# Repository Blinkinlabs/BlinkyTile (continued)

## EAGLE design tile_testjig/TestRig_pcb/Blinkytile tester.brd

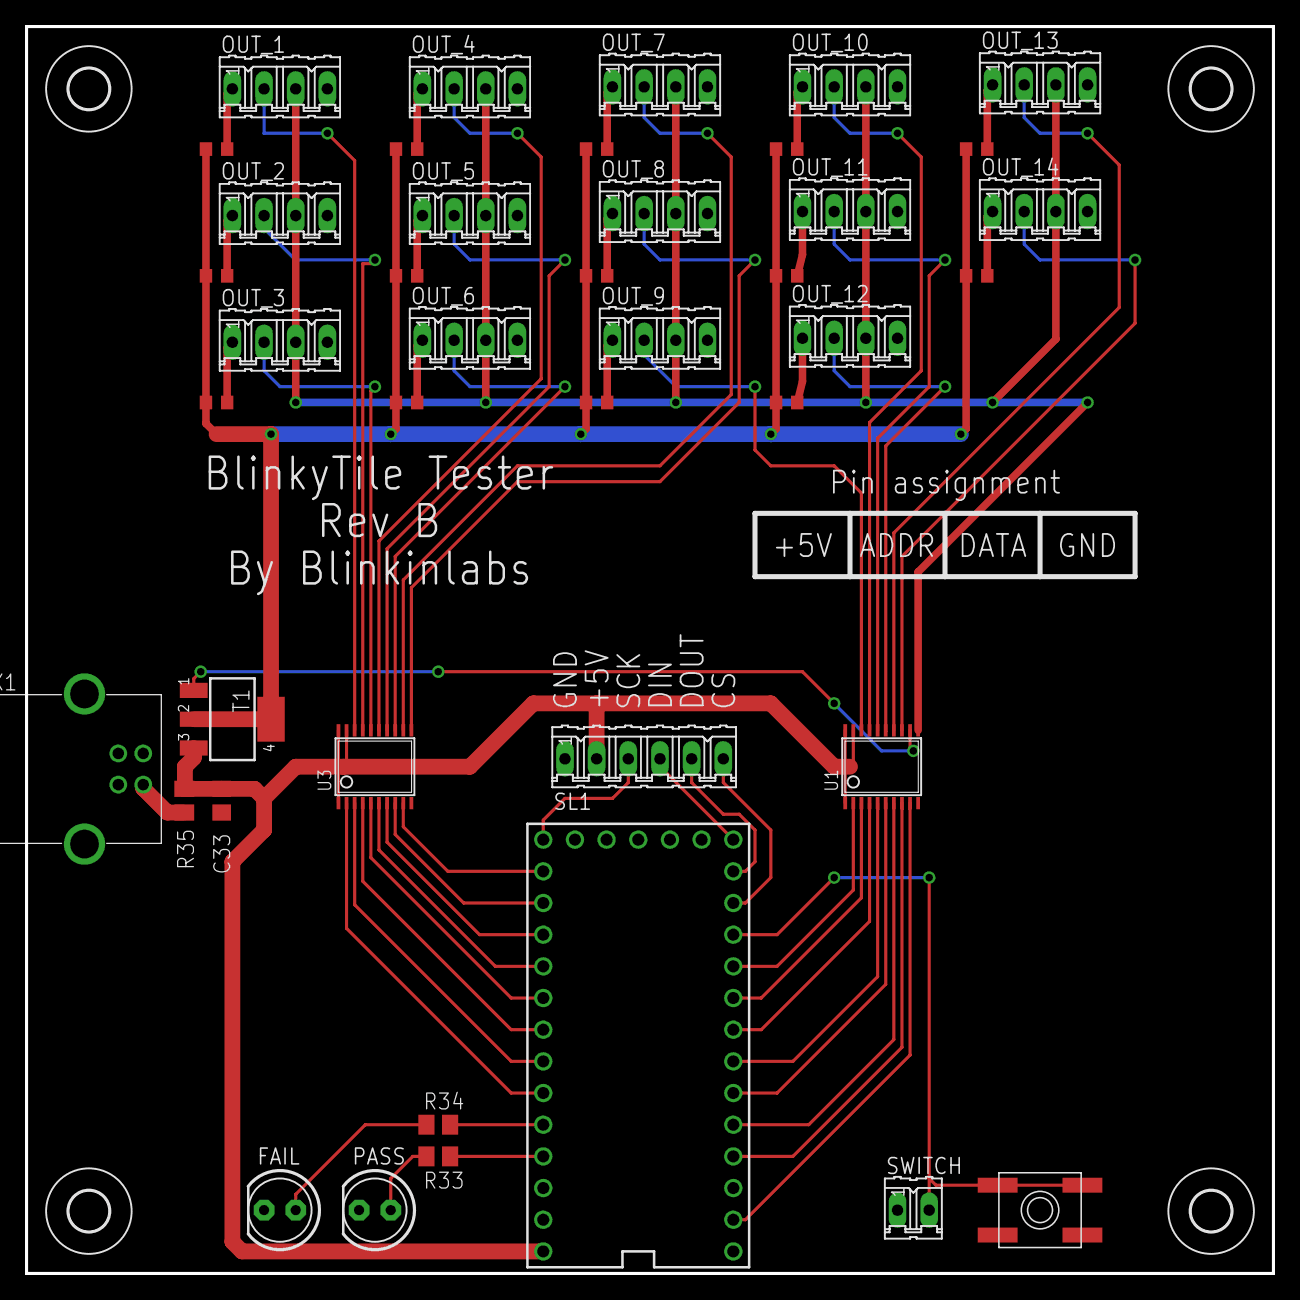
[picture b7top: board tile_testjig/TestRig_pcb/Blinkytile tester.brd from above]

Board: 2 copper layers, 100.0 x 100.0 mm, 46 parts (0 on the bottom side), 60 nets.

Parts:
C33: 0.1uF; C0805
FAIL: LED5MM
H1, H2, H3, H4: MOUNT-HOLE3.2; 3,2
OUT_1, OUT_2, OUT_3, OUT_4, OUT_5, OUT_6, OUT_7, OUT_8, OUT_9, OUT_10, OUT_11, OUT_12, OUT_13, OUT_14: 04P
PASS: LED5MM
R1, R2, R3, R4, R5, R6, R7, R8, R9, R10, R11, R12, R13, R14: 50; R0603
R33, R34, R35: M0805
SL1: 06P
SW1: SPST_TACT-EVQQ2; EVQ-Q2
SWITCH: 02P
T1: SOT223
U1, U3: SN74HCT245PWR; TSSOP20
U$1: TEENSY_3.0_BASIC
X1: MINI-USB_4P-85-32004-10X; 85-32004-10X

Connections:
3.3V: U$1.3.3V, U$1.3.3V1
5V_B: R1.1, R2.1, R3.1, R4.1, R5.1, R6.1, R7.1, R8.1, R9.1, R10.1, R11.1, R12.1, R13.1, R14.1, T1.2, T1.4
+5V: C33.1, R35.2, SL1.2, T1.3, U1.1, U1.19, U1.20, U3.1, U3.19, U3.20, U$1.VIN
ADDR1: U3.2, U$1.21/A7
ADDR1_B: OUT_1.2, U3.18
ADDR2: U3.3, U$1.20/A6
ADDR2_B: OUT_2.2, U3.17
ADDR3: U3.4, U$1.19/A5
ADDR3_B: OUT_3.2, U3.16
ADDR4: U3.5, U$1.18/A4
ADDR4_B: OUT_4.2, U3.15
ADDR5: U3.6, U$1.17/A3
ADDR5_B: OUT_5.2, U3.14
ADDR6: U3.7, U$1.16/A2
ADDR6_B: OUT_6.2, U3.13
ADDR7: U3.8, U$1.15/A1
ADDR7_B: OUT_7.2, U3.12
ADDR8: U3.9, U$1.14/A0
ADDR8_B: OUT_8.2, U3.11
ADDR9: U1.2, U$1.8
ADDR9_B: OUT_9.2, U1.18
ADDR10: U1.3, U$1.7
ADDR10_B: OUT_10.2, U1.17
ADDR11: U1.4, U$1.6
ADDR11_B: OUT_11.2, U1.16
ADDR12: U1.5, U$1.5
ADDR12_B: OUT_12.2, U1.15
ADDR13: U1.6, U$1.4
ADDR13_B: OUT_13.2, U1.14
ADDR14: U1.7, U$1.3
ADDR14_B: OUT_14.2, U1.13
CS: SL1.6, U$1.10
DATA: U1.9, U$1.0
DATA_B: OUT_1.3, OUT_2.3, OUT_3.3, OUT_4.3, OUT_5.3, OUT_6.3, OUT_7.3, OUT_8.3, OUT_9.3, OUT_10.3, OUT_11.3, OUT_12.3, OUT_13.3, OUT_14.3, U1.11
DIN: SL1.4, U$1.12
DOUT: SL1.5, U$1.11
GND: C33.2, FAIL.K, OUT_1.4, OUT_2.4, OUT_3.4, OUT_4.4, OUT_5.4, OUT_6.4, OUT_7.4, OUT_8.4, OUT_9.4, OUT_10.4, OUT_11.4, OUT_12.4, OUT_13.4, OUT_14.4, PASS.K, SL1.1, SW1.A, SW1.A', SWITCH.1, U1.10, U3.10, U$1.AGND, U$1.GND, U$1.GND1, X1.4
GOOD: PASS.A, R33.1
unnamed: OUT_5.1, R5.2
unnamed: OUT_1.1, R1.2
unnamed: SW1.B, SW1.B', SWITCH.2, U$1.9
unnamed: OUT_2.1, R2.2
unnamed: OUT_3.1, R3.2
unnamed: OUT_4.1, R4.2
unnamed: OUT_6.1, R6.2
unnamed: OUT_7.1, R7.2
unnamed: OUT_8.1, R8.2
unnamed: OUT_9.1, R9.2
unnamed: OUT_10.1, R10.2
unnamed: OUT_11.1, R11.2
unnamed: OUT_13.1, R13.2
unnamed: OUT_14.1, R14.2
unnamed: OUT_12.1, R12.2
unnamed: R33.2, U$1.23/A9
unnamed: R34.2, U$1.22/A8
unnamed: FAIL.A, R34.1
unnamed: R35.1, X1.1
PWR_EN: U1.8, U$1.2
PWR_EN_B: T1.1, U1.12
SCK: SL1.3, U$1.13

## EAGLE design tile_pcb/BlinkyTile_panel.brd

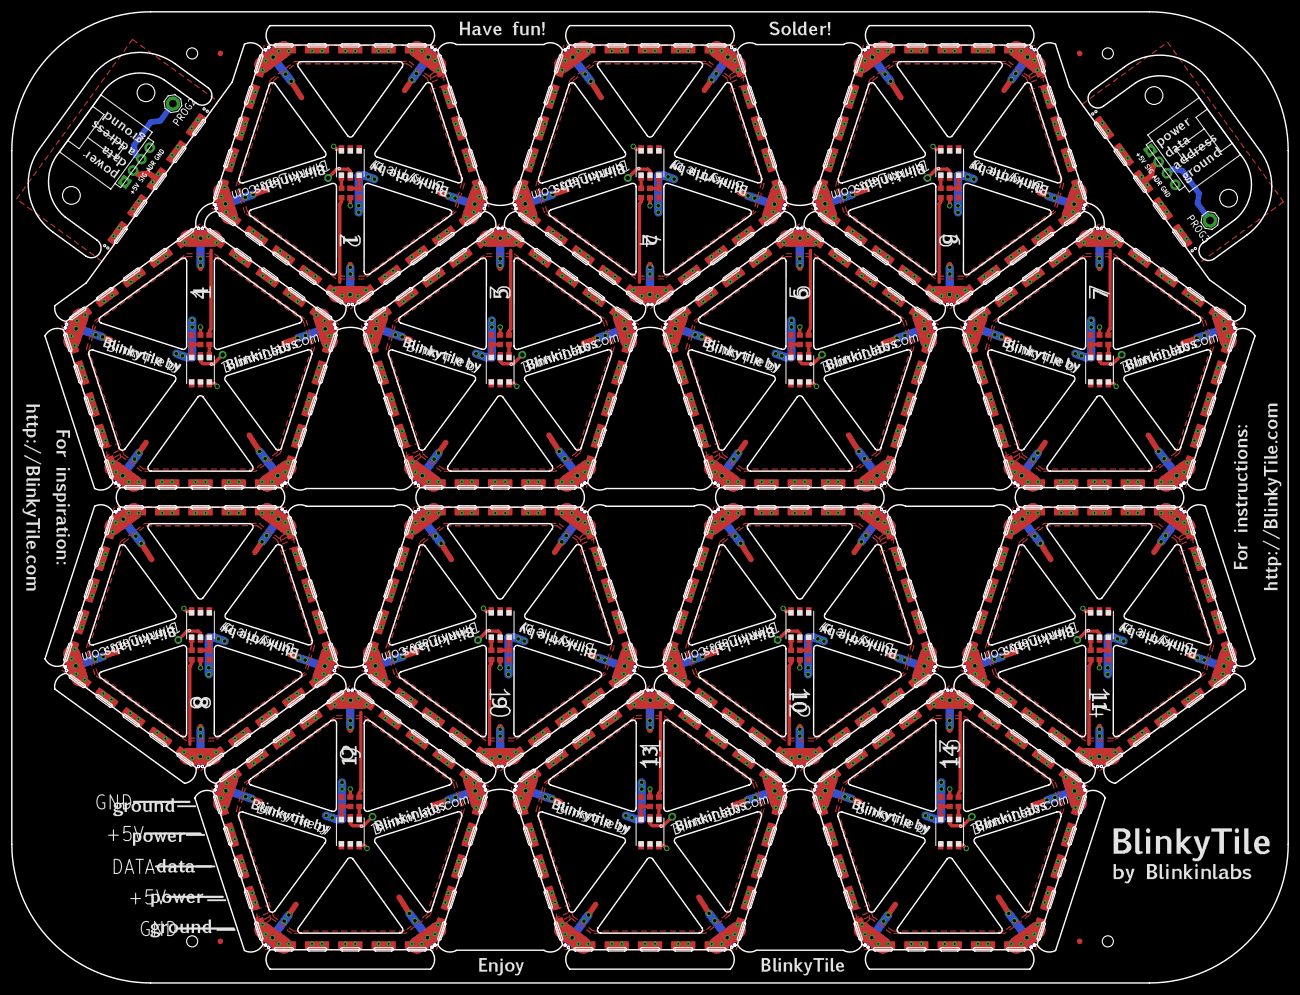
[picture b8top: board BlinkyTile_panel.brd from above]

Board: 2 copper layers, 230.0 x 175.0 mm, 322 parts (0 on the bottom side), 78 nets.

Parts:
C2, C3, C4, C5, C6, C7, C8, C9, C10, C11, C12, C13, C14, C15: .1uF; C0603
E$1, E$2, E$221, E$224: FIDUCIAL-1X2
E$23, E$24, E$25, E$26, E$27, E$28, E$29, E$30, E$31, E$32, E$33, E$34, E$35, E$36, E$37, E$38, E$39, E$40, E$41, E$42, E$43, E$44, E$45, E$46, E$49, E$50, E$51, E$52, E$53, E$54, E$56, E$57, E$58, E$59, E$60, E$61, E$62, E$63, E$64, E$65, E$66, E$67, E$68, E$69, E$70, E$71, E$72, E$73, E$74, E$75, E$76, E$77, E$78, E$79, E$80, E$81, E$82, E$83, E$84, E$85, E$86, E$87, E$88, E$89, E$90, E$91, E$92, E$93, E$94, E$95, E$96, E$97, E$98, E$99, E$100, E$101, E$102, E$103, E$104, E$105, E$106, E$107, E$108, E$109, E$110, E$111, E$112, E$113, E$114, E$115, E$116, E$117, E$118, E$119, E$120, E$121, E$122, E$123, E$124, E$125, E$126, E$127, E$128, E$129, E$130, E$131, E$132, E$133, E$134, E$135, E$136, E$137, E$138, E$139, E$140, E$141, E$142, E$143, E$144, E$145, E$146, E$147, E$148, E$149, E$150, E$151, E$152, E$153, E$154, E$155, E$156, E$157, E$158, E$159, E$160, E$161, E$162, E$163, E$164, E$165, E$166, E$167, E$168, E$169, E$170, E$171, E$172, E$173, E$174, E$175, E$176, E$177, E$178, E$179, E$180, E$181, E$182, E$183, E$184, E$185, E$186, E$187, E$188, E$189, E$190, E$191, E$192, E$193, E$199, E$200, E$202, E$203: MOUSE_BITE_1
E$201, E$204: 4-PIN_DUPONT
E$205, E$206, E$207, E$208, E$209, E$210, E$211, E$212, E$213, E$214, E$215, E$216, E$217, E$218: BLINKYTILE
PROG2, PROG3: SE14
R3, R5, R7, R9, R11, R13, R15, R17, R19, R21, R23, R25, R27, R29: 75; R0603
R4, R6, R8, R10, R12, R14, R16, R18, R20, R22, R24, R26, R28, R30: 10k; R0603
U$1, U$8, U$9, U$10, U$11, U$13, U$14, U$15, U$16, U$17, U$19, U$20, U$21, U$22, U$23, U$25, U$26, U$27, U$28, U$29, U$31, U$32, U$33, U$34, U$35, U$37, U$38, U$39, U$40, U$41, U$43, U$44, U$45, U$46, U$47, U$49, U$50, U$51, U$52, U$53, U$55, U$56, U$57, U$58, U$59, U$61, U$62, U$63, U$64, U$65, U$67, U$68, U$69, U$70, U$71, U$73, U$74, U$75, U$76, U$77, U$79, U$80, U$81, U$82, U$83, U$85, U$86, U$87, U$88, U$89, U$93, U$94: D_EDGEMOD; D_EDGE_SLOT_MOD
U$12, U$18, U$24, U$30, U$36, U$42, U$48, U$54, U$60, U$66, U$72, U$78, U$84, U$90: WS2822S_LED

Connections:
5V2: R3.1, U$1.P$2, U$1.P$4, U$1.P$7, U$1.P$9, U$1.PWRVIA1, U$1.PWRVIA3, U$1.PWRVIA4, U$1.PWRVIA6, U$8.P$2, U$8.P$4, U$8.P$7, U$8.P$9, U$8.PWRVIA1, U$8.PWRVIA3, U$8.PWRVIA4, U$8.PWRVIA6, U$9.P$2, U$9.P$4, U$9.P$7, U$9.P$9, U$9.PWRVIA1, U$9.PWRVIA3, U$9.PWRVIA4, U$9.PWRVIA6, U$10.P$2, U$10.P$4, U$10.P$7, U$10.P$9, U$10.PWRVIA1, U$10.PWRVIA3, U$10.PWRVIA4, U$10.PWRVIA6, U$11.P$2, U$11.P$4, U$11.P$7, U$11.P$9, U$11.PWRVIA1, U$11.PWRVIA3, U$11.PWRVIA4, U$11.PWRVIA6, U$12.6
5V3: R5.1, U$13.P$2, U$13.P$4, U$13.P$7, U$13.P$9, U$13.PWRVIA1, U$13.PWRVIA3, U$13.PWRVIA4, U$13.PWRVIA6, U$14.P$2, U$14.P$4, U$14.P$7, U$14.P$9, U$14.PWRVIA1, U$14.PWRVIA3, U$14.PWRVIA4, U$14.PWRVIA6, U$15.P$2, U$15.P$4, U$15.P$7, U$15.P$9, U$15.PWRVIA1, U$15.PWRVIA3, U$15.PWRVIA4, U$15.PWRVIA6, U$16.P$2, U$16.P$4, U$16.P$7, U$16.P$9, U$16.PWRVIA1, U$16.PWRVIA3, U$16.PWRVIA4, U$16.PWRVIA6, U$17.P$2, U$17.P$4, U$17.P$7, U$17.P$9, U$17.PWRVIA1, U$17.PWRVIA3, U$17.PWRVIA4, U$17.PWRVIA6, U$18.6
5V4: R7.1, U$19.P$2, U$19.P$4, U$19.P$7, U$19.P$9, U$19.PWRVIA1, U$19.PWRVIA3, U$19.PWRVIA4, U$19.PWRVIA6, U$20.P$2, U$20.P$4, U$20.P$7, U$20.P$9, U$20.PWRVIA1, U$20.PWRVIA3, U$20.PWRVIA4, U$20.PWRVIA6, U$21.P$2, U$21.P$4, U$21.P$7, U$21.P$9, U$21.PWRVIA1, U$21.PWRVIA3, U$21.PWRVIA4, U$21.PWRVIA6, U$22.P$2, U$22.P$4, U$22.P$7, U$22.P$9, U$22.PWRVIA1, U$22.PWRVIA3, U$22.PWRVIA4, U$22.PWRVIA6, U$23.P$2, U$23.P$4, U$23.P$7, U$23.P$9, U$23.PWRVIA1, U$23.PWRVIA3, U$23.PWRVIA4, U$23.PWRVIA6, U$24.6
5V5: R9.1, U$25.P$2, U$25.P$4, U$25.P$7, U$25.P$9, U$25.PWRVIA1, U$25.PWRVIA3, U$25.PWRVIA4, U$25.PWRVIA6, U$26.P$2, U$26.P$4, U$26.P$7, U$26.P$9, U$26.PWRVIA1, U$26.PWRVIA3, U$26.PWRVIA4, U$26.PWRVIA6, U$27.P$2, U$27.P$4, U$27.P$7, U$27.P$9, U$27.PWRVIA1, U$27.PWRVIA3, U$27.PWRVIA4, U$27.PWRVIA6, U$28.P$2, U$28.P$4, U$28.P$7, U$28.P$9, U$28.PWRVIA1, U$28.PWRVIA3, U$28.PWRVIA4, U$28.PWRVIA6, U$29.P$2, U$29.P$4, U$29.P$7, U$29.P$9, U$29.PWRVIA1, U$29.PWRVIA3, U$29.PWRVIA4, U$29.PWRVIA6, U$30.6
5V6: R11.1, U$31.P$2, U$31.P$4, U$31.P$7, U$31.P$9, U$31.PWRVIA1, U$31.PWRVIA3, U$31.PWRVIA4, U$31.PWRVIA6, U$32.P$2, U$32.P$4, U$32.P$7, U$32.P$9, U$32.PWRVIA1, U$32.PWRVIA3, U$32.PWRVIA4, U$32.PWRVIA6, U$33.P$2, U$33.P$4, U$33.P$7, U$33.P$9, U$33.PWRVIA1, U$33.PWRVIA3, U$33.PWRVIA4, U$33.PWRVIA6, U$34.P$2, U$34.P$4, U$34.P$7, U$34.P$9, U$34.PWRVIA1, U$34.PWRVIA3, U$34.PWRVIA4, U$34.PWRVIA6, U$35.P$2, U$35.P$4, U$35.P$7, U$35.P$9, U$35.PWRVIA1, U$35.PWRVIA3, U$35.PWRVIA4, U$35.PWRVIA6, U$36.6
5V7: R13.1, U$37.P$2, U$37.P$4, U$37.P$7, U$37.P$9, U$37.PWRVIA1, U$37.PWRVIA3, U$37.PWRVIA4, U$37.PWRVIA6, U$38.P$2, U$38.P$4, U$38.P$7, U$38.P$9, U$38.PWRVIA1, U$38.PWRVIA3, U$38.PWRVIA4, U$38.PWRVIA6, U$39.P$2, U$39.P$4, U$39.P$7, U$39.P$9, U$39.PWRVIA1, U$39.PWRVIA3, U$39.PWRVIA4, U$39.PWRVIA6, U$40.P$2, U$40.P$4, U$40.P$7, U$40.P$9, U$40.PWRVIA1, U$40.PWRVIA3, U$40.PWRVIA4, U$40.PWRVIA6, U$41.P$2, U$41.P$4, U$41.P$7, U$41.P$9, U$41.PWRVIA1, U$41.PWRVIA3, U$41.PWRVIA4, U$41.PWRVIA6, U$42.6
5V8: R15.1, U$43.P$2, U$43.P$4, U$43.P$7, U$43.P$9, U$43.PWRVIA1, U$43.PWRVIA3, U$43.PWRVIA4, U$43.PWRVIA6, U$44.P$2, U$44.P$4, U$44.P$7, U$44.P$9, U$44.PWRVIA1, U$44.PWRVIA3, U$44.PWRVIA4, U$44.PWRVIA6, U$45.P$2, U$45.P$4, U$45.P$7, U$45.P$9, U$45.PWRVIA1, U$45.PWRVIA3, U$45.PWRVIA4, U$45.PWRVIA6, U$46.P$2, U$46.P$4, U$46.P$7, U$46.P$9, U$46.PWRVIA1, U$46.PWRVIA3, U$46.PWRVIA4, U$46.PWRVIA6, U$47.P$2, U$47.P$4, U$47.P$7, U$47.P$9, U$47.PWRVIA1, U$47.PWRVIA3, U$47.PWRVIA4, U$47.PWRVIA6, U$48.6
5V9: R17.1, U$49.P$2, U$49.P$4, U$49.P$7, U$49.P$9, U$49.PWRVIA1, U$49.PWRVIA3, U$49.PWRVIA4, U$49.PWRVIA6, U$50.P$2, U$50.P$4, U$50.P$7, U$50.P$9, U$50.PWRVIA1, U$50.PWRVIA3, U$50.PWRVIA4, U$50.PWRVIA6, U$51.P$2, U$51.P$4, U$51.P$7, U$51.P$9, U$51.PWRVIA1, U$51.PWRVIA3, U$51.PWRVIA4, U$51.PWRVIA6, U$52.P$2, U$52.P$4, U$52.P$7, U$52.P$9, U$52.PWRVIA1, U$52.PWRVIA3, U$52.PWRVIA4, U$52.PWRVIA6, U$53.P$2, U$53.P$4, U$53.P$7, U$53.P$9, U$53.PWRVIA1, U$53.PWRVIA3, U$53.PWRVIA4, U$53.PWRVIA6, U$54.6
5V10: R19.1, U$55.P$2, U$55.P$4, U$55.P$7, U$55.P$9, U$55.PWRVIA1, U$55.PWRVIA3, U$55.PWRVIA4, U$55.PWRVIA6, U$56.P$2, U$56.P$4, U$56.P$7, U$56.P$9, U$56.PWRVIA1, U$56.PWRVIA3, U$56.PWRVIA4, U$56.PWRVIA6, U$57.P$2, U$57.P$4, U$57.P$7, U$57.P$9, U$57.PWRVIA1, U$57.PWRVIA3, U$57.PWRVIA4, U$57.PWRVIA6, U$58.P$2, U$58.P$4, U$58.P$7, U$58.P$9, U$58.PWRVIA1, U$58.PWRVIA3, U$58.PWRVIA4, U$58.PWRVIA6, U$59.P$2, U$59.P$4, U$59.P$7, U$59.P$9, U$59.PWRVIA1, U$59.PWRVIA3, U$59.PWRVIA4, U$59.PWRVIA6, U$60.6
5V11: R21.1, U$61.P$2, U$61.P$4, U$61.P$7, U$61.P$9, U$61.PWRVIA1, U$61.PWRVIA3, U$61.PWRVIA4, U$61.PWRVIA6, U$62.P$2, U$62.P$4, U$62.P$7, U$62.P$9, U$62.PWRVIA1, U$62.PWRVIA3, U$62.PWRVIA4, U$62.PWRVIA6, U$63.P$2, U$63.P$4, U$63.P$7, U$63.P$9, U$63.PWRVIA1, U$63.PWRVIA3, U$63.PWRVIA4, U$63.PWRVIA6, U$64.P$2, U$64.P$4, U$64.P$7, U$64.P$9, U$64.PWRVIA1, U$64.PWRVIA3, U$64.PWRVIA4, U$64.PWRVIA6, U$65.P$2, U$65.P$4, U$65.P$7, U$65.P$9, U$65.PWRVIA1, U$65.PWRVIA3, U$65.PWRVIA4, U$65.PWRVIA6, U$66.6
5V12: R23.1, U$67.P$2, U$67.P$4, U$67.P$7, U$67.P$9, U$67.PWRVIA1, U$67.PWRVIA3, U$67.PWRVIA4, U$67.PWRVIA6, U$68.P$2, U$68.P$4, U$68.P$7, U$68.P$9, U$68.PWRVIA1, U$68.PWRVIA3, U$68.PWRVIA4, U$68.PWRVIA6, U$69.P$2, U$69.P$4, U$69.P$7, U$69.P$9, U$69.PWRVIA1, U$69.PWRVIA3, U$69.PWRVIA4, U$69.PWRVIA6, U$70.P$2, U$70.P$4, U$70.P$7, U$70.P$9, U$70.PWRVIA1, U$70.PWRVIA3, U$70.PWRVIA4, U$70.PWRVIA6, U$71.P$2, U$71.P$4, U$71.P$7, U$71.P$9, U$71.PWRVIA1, U$71.PWRVIA3, U$71.PWRVIA4, U$71.PWRVIA6, U$72.6
5V13: R25.1, U$73.P$2, U$73.P$4, U$73.P$7, U$73.P$9, U$73.PWRVIA1, U$73.PWRVIA3, U$73.PWRVIA4, U$73.PWRVIA6, U$74.P$2, U$74.P$4, U$74.P$7, U$74.P$9, U$74.PWRVIA1, U$74.PWRVIA3, U$74.PWRVIA4, U$74.PWRVIA6, U$75.P$2, U$75.P$4, U$75.P$7, U$75.P$9, U$75.PWRVIA1, U$75.PWRVIA3, U$75.PWRVIA4, U$75.PWRVIA6, U$76.P$2, U$76.P$4, U$76.P$7, U$76.P$9, U$76.PWRVIA1, U$76.PWRVIA3, U$76.PWRVIA4, U$76.PWRVIA6, U$77.P$2, U$77.P$4, U$77.P$7, U$77.P$9, U$77.PWRVIA1, U$77.PWRVIA3, U$77.PWRVIA4, U$77.PWRVIA6, U$78.6
5V14: R27.1, U$79.P$2, U$79.P$4, U$79.P$7, U$79.P$9, U$79.PWRVIA1, U$79.PWRVIA3, U$79.PWRVIA4, U$79.PWRVIA6, U$80.P$2, U$80.P$4, U$80.P$7, U$80.P$9, U$80.PWRVIA1, U$80.PWRVIA3, U$80.PWRVIA4, U$80.PWRVIA6, U$81.P$2, U$81.P$4, U$81.P$7, U$81.P$9, U$81.PWRVIA1, U$81.PWRVIA3, U$81.PWRVIA4, U$81.PWRVIA6, U$82.P$2, U$82.P$4, U$82.P$7, U$82.P$9, U$82.PWRVIA1, U$82.PWRVIA3, U$82.PWRVIA4, U$82.PWRVIA6, U$83.P$2, U$83.P$4, U$83.P$7, U$83.P$9, U$83.PWRVIA1, U$83.PWRVIA3, U$83.PWRVIA4, U$83.PWRVIA6, U$84.6
5V15: R29.1, U$85.P$2, U$85.P$4, U$85.P$7, U$85.P$9, U$85.PWRVIA1, U$85.PWRVIA3, U$85.PWRVIA4, U$85.PWRVIA6, U$86.P$2, U$86.P$4, U$86.P$7, U$86.P$9, U$86.PWRVIA1, U$86.PWRVIA3, U$86.PWRVIA4, U$86.PWRVIA6, U$87.P$2, U$87.P$4, U$87.P$7, U$87.P$9, U$87.PWRVIA1, U$87.PWRVIA3, U$87.PWRVIA4, U$87.PWRVIA6, U$88.P$2, U$88.P$4, U$88.P$7, U$88.P$9, U$88.PWRVIA1, U$88.PWRVIA3, U$88.PWRVIA4, U$88.PWRVIA6, U$89.P$2, U$89.P$4, U$89.P$7, U$89.P$9, U$89.PWRVIA1, U$89.PWRVIA3, U$89.PWRVIA4, U$89.PWRVIA6, U$90.6
DATA1: R4.2, U$1.P$3, U$1.P$8, U$1.SIGVIA1, U$1.SIGVIA3, U$8.P$3, U$8.P$8, U$8.SIGVIA1, U$8.SIGVIA3, U$9.P$3, U$9.P$8, U$9.SIGVIA1, U$9.SIGVIA3, U$10.P$3, U$10.P$8, U$10.SIGVIA1, U$10.SIGVIA3, U$11.P$3, U$11.P$8, U$11.SIGVIA1, U$11.SIGVIA3
DATA2: R6.2, U$13.P$3, U$13.P$8, U$13.SIGVIA1, U$13.SIGVIA3, U$14.P$3, U$14.P$8, U$14.SIGVIA1, U$14.SIGVIA3, U$15.P$3, U$15.P$8, U$15.SIGVIA1, U$15.SIGVIA3, U$16.P$3, U$16.P$8, U$16.SIGVIA1, U$16.SIGVIA3, U$17.P$3, U$17.P$8, U$17.SIGVIA1, U$17.SIGVIA3
DATA3: R8.2, U$19.P$3, U$19.P$8, U$19.SIGVIA1, U$19.SIGVIA3, U$20.P$3, U$20.P$8, U$20.SIGVIA1, U$20.SIGVIA3, U$21.P$3, U$21.P$8, U$21.SIGVIA1, U$21.SIGVIA3, U$22.P$3, U$22.P$8, U$22.SIGVIA1, U$22.SIGVIA3, U$23.P$3, U$23.P$8, U$23.SIGVIA1, U$23.SIGVIA3
DATA4: R10.2, U$25.P$3, U$25.P$8, U$25.SIGVIA1, U$25.SIGVIA3, U$26.P$3, U$26.P$8, U$26.SIGVIA1, U$26.SIGVIA3, U$27.P$3, U$27.P$8, U$27.SIGVIA1, U$27.SIGVIA3, U$28.P$3, U$28.P$8, U$28.SIGVIA1, U$28.SIGVIA3, U$29.P$3, U$29.P$8, U$29.SIGVIA1, U$29.SIGVIA3
DATA5: R12.2, U$31.P$3, U$31.P$8, U$31.SIGVIA1, U$31.SIGVIA3, U$32.P$3, U$32.P$8, U$32.SIGVIA1, U$32.SIGVIA3, U$33.P$3, U$33.P$8, U$33.SIGVIA1, U$33.SIGVIA3, U$34.P$3, U$34.P$8, U$34.SIGVIA1, U$34.SIGVIA3, U$35.P$3, U$35.P$8, U$35.SIGVIA1, U$35.SIGVIA3
DATA6: R14.2, U$37.P$3, U$37.P$8, U$37.SIGVIA1, U$37.SIGVIA3, U$38.P$3, U$38.P$8, U$38.SIGVIA1, U$38.SIGVIA3, U$39.P$3, U$39.P$8, U$39.SIGVIA1, U$39.SIGVIA3, U$40.P$3, U$40.P$8, U$40.SIGVIA1, U$40.SIGVIA3, U$41.P$3, U$41.P$8, U$41.SIGVIA1, U$41.SIGVIA3
DATA7: R16.2, U$43.P$3, U$43.P$8, U$43.SIGVIA1, U$43.SIGVIA3, U$44.P$3, U$44.P$8, U$44.SIGVIA1, U$44.SIGVIA3, U$45.P$3, U$45.P$8, U$45.SIGVIA1, U$45.SIGVIA3, U$46.P$3, U$46.P$8, U$46.SIGVIA1, U$46.SIGVIA3, U$47.P$3, U$47.P$8, U$47.SIGVIA1, U$47.SIGVIA3
DATA8: R18.2, U$49.P$3, U$49.P$8, U$49.SIGVIA1, U$49.SIGVIA3, U$50.P$3, U$50.P$8, U$50.SIGVIA1, U$50.SIGVIA3, U$51.P$3, U$51.P$8, U$51.SIGVIA1, U$51.SIGVIA3, U$52.P$3, U$52.P$8, U$52.SIGVIA1, U$52.SIGVIA3, U$53.P$3, U$53.P$8, U$53.SIGVIA1, U$53.SIGVIA3
DATA9: R20.2, U$55.P$3, U$55.P$8, U$55.SIGVIA1, U$55.SIGVIA3, U$56.P$3, U$56.P$8, U$56.SIGVIA1, U$56.SIGVIA3, U$57.P$3, U$57.P$8, U$57.SIGVIA1, U$57.SIGVIA3, U$58.P$3, U$58.P$8, U$58.SIGVIA1, U$58.SIGVIA3, U$59.P$3, U$59.P$8, U$59.SIGVIA1, U$59.SIGVIA3
DATA10: R22.2, U$61.P$3, U$61.P$8, U$61.SIGVIA1, U$61.SIGVIA3, U$62.P$3, U$62.P$8, U$62.SIGVIA1, U$62.SIGVIA3, U$63.P$3, U$63.P$8, U$63.SIGVIA1, U$63.SIGVIA3, U$64.P$3, U$64.P$8, U$64.SIGVIA1, U$64.SIGVIA3, U$65.P$3, U$65.P$8, U$65.SIGVIA1, U$65.SIGVIA3
DATA11: R24.2, U$67.P$3, U$67.P$8, U$67.SIGVIA1, U$67.SIGVIA3, U$68.P$3, U$68.P$8, U$68.SIGVIA1, U$68.SIGVIA3, U$69.P$3, U$69.P$8, U$69.SIGVIA1, U$69.SIGVIA3, U$70.P$3, U$70.P$8, U$70.SIGVIA1, U$70.SIGVIA3, U$71.P$3, U$71.P$8, U$71.SIGVIA1, U$71.SIGVIA3
DATA12: R26.2, U$73.P$3, U$73.P$8, U$73.SIGVIA1, U$73.SIGVIA3, U$74.P$3, U$74.P$8, U$74.SIGVIA1, U$74.SIGVIA3, U$75.P$3, U$75.P$8, U$75.SIGVIA1, U$75.SIGVIA3, U$76.P$3, U$76.P$8, U$76.SIGVIA1, U$76.SIGVIA3, U$77.P$3, U$77.P$8, U$77.SIGVIA1, U$77.SIGVIA3
DATA13: R28.2, U$79.P$3, U$79.P$8, U$79.SIGVIA1, U$79.SIGVIA3, U$80.P$3, U$80.P$8, U$80.SIGVIA1, U$80.SIGVIA3, U$81.P$3, U$81.P$8, U$81.SIGVIA1, U$81.SIGVIA3, U$82.P$3, U$82.P$8, U$82.SIGVIA1, U$82.SIGVIA3, U$83.P$3, U$83.P$8, U$83.SIGVIA1, U$83.SIGVIA3
DATA14: R30.2, U$85.P$3, U$85.P$8, U$85.SIGVIA1, U$85.SIGVIA3, U$86.P$3, U$86.P$8, U$86.SIGVIA1, U$86.SIGVIA3, U$87.P$3, U$87.P$8, U$87.SIGVIA1, U$87.SIGVIA3, U$88.P$3, U$88.P$8, U$88.SIGVIA1, U$88.SIGVIA3, U$89.P$3, U$89.P$8, U$89.SIGVIA1, U$89.SIGVIA3
GND1: C2.2, U$1.GNDVIA1, U$1.GNDVIA3, U$1.GNDVIA4, U$1.GNDVIA6, U$1.P$1, U$1.P$5, U$1.P$6, U$1.P$10, U$8.GNDVIA1, U$8.GNDVIA3, U$8.GNDVIA4, U$8.GNDVIA6, U$8.P$1, U$8.P$5, U$8.P$6, U$8.P$10, U$9.GNDVIA1, U$9.GNDVIA3, U$9.GNDVIA4, U$9.GNDVIA6, U$9.P$1, U$9.P$5, U$9.P$6, U$9.P$10, U$10.GNDVIA1, U$10.GNDVIA3, U$10.GNDVIA4, U$10.GNDVIA6, U$10.P$1, U$10.P$5, U$10.P$6, U$10.P$10, U$11.GNDVIA1, U$11.GNDVIA3, U$11.GNDVIA4, U$11.GNDVIA6, U$11.P$1, U$11.P$5, U$11.P$6, U$11.P$10, U$12.4
GND2: C3.2, U$13.GNDVIA1, U$13.GNDVIA3, U$13.GNDVIA4, U$13.GNDVIA6, U$13.P$1, U$13.P$5, U$13.P$6, U$13.P$10, U$14.GNDVIA1, U$14.GNDVIA3, U$14.GNDVIA4, U$14.GNDVIA6, U$14.P$1, U$14.P$5, U$14.P$6, U$14.P$10, U$15.GNDVIA1, U$15.GNDVIA3, U$15.GNDVIA4, U$15.GNDVIA6, U$15.P$1, U$15.P$5, U$15.P$6, U$15.P$10, U$16.GNDVIA1, U$16.GNDVIA3, U$16.GNDVIA4, U$16.GNDVIA6, U$16.P$1, U$16.P$5, U$16.P$6, U$16.P$10, U$17.GNDVIA1, U$17.GNDVIA3, U$17.GNDVIA4, U$17.GNDVIA6, U$17.P$1, U$17.P$5, U$17.P$6, U$17.P$10, U$18.4
GND3: C4.2, U$19.GNDVIA1, U$19.GNDVIA3, U$19.GNDVIA4, U$19.GNDVIA6, U$19.P$1, U$19.P$5, U$19.P$6, U$19.P$10, U$20.GNDVIA1, U$20.GNDVIA3, U$20.GNDVIA4, U$20.GNDVIA6, U$20.P$1, U$20.P$5, U$20.P$6, U$20.P$10, U$21.GNDVIA1, U$21.GNDVIA3, U$21.GNDVIA4, U$21.GNDVIA6, U$21.P$1, U$21.P$5, U$21.P$6, U$21.P$10, U$22.GNDVIA1, U$22.GNDVIA3, U$22.GNDVIA4, U$22.GNDVIA6, U$22.P$1, U$22.P$5, U$22.P$6, U$22.P$10, U$23.GNDVIA1, U$23.GNDVIA3, U$23.GNDVIA4, U$23.GNDVIA6, U$23.P$1, U$23.P$5, U$23.P$6, U$23.P$10, U$24.4
GND4: C5.2, U$25.GNDVIA1, U$25.GNDVIA3, U$25.GNDVIA4, U$25.GNDVIA6, U$25.P$1, U$25.P$5, U$25.P$6, U$25.P$10, U$26.GNDVIA1, U$26.GNDVIA3, U$26.GNDVIA4, U$26.GNDVIA6, U$26.P$1, U$26.P$5, U$26.P$6, U$26.P$10, U$27.GNDVIA1, U$27.GNDVIA3, U$27.GNDVIA4, U$27.GNDVIA6, U$27.P$1, U$27.P$5, U$27.P$6, U$27.P$10, U$28.GNDVIA1, U$28.GNDVIA3, U$28.GNDVIA4, U$28.GNDVIA6, U$28.P$1, U$28.P$5, U$28.P$6, U$28.P$10, U$29.GNDVIA1, U$29.GNDVIA3, U$29.GNDVIA4, U$29.GNDVIA6, U$29.P$1, U$29.P$5, U$29.P$6, U$29.P$10, U$30.4
GND5: C6.2, U$31.GNDVIA1, U$31.GNDVIA3, U$31.GNDVIA4, U$31.GNDVIA6, U$31.P$1, U$31.P$5, U$31.P$6, U$31.P$10, U$32.GNDVIA1, U$32.GNDVIA3, U$32.GNDVIA4, U$32.GNDVIA6, U$32.P$1, U$32.P$5, U$32.P$6, U$32.P$10, U$33.GNDVIA1, U$33.GNDVIA3, U$33.GNDVIA4, U$33.GNDVIA6, U$33.P$1, U$33.P$5, U$33.P$6, U$33.P$10, U$34.GNDVIA1, U$34.GNDVIA3, U$34.GNDVIA4, U$34.GNDVIA6, U$34.P$1, U$34.P$5, U$34.P$6, U$34.P$10, U$35.GNDVIA1, U$35.GNDVIA3, U$35.GNDVIA4, U$35.GNDVIA6, U$35.P$1, U$35.P$5, U$35.P$6, U$35.P$10, U$36.4
GND6: C7.2, U$37.GNDVIA1, U$37.GNDVIA3, U$37.GNDVIA4, U$37.GNDVIA6, U$37.P$1, U$37.P$5, U$37.P$6, U$37.P$10, U$38.GNDVIA1, U$38.GNDVIA3, U$38.GNDVIA4, U$38.GNDVIA6, U$38.P$1, U$38.P$5, U$38.P$6, U$38.P$10, U$39.GNDVIA1, U$39.GNDVIA3, U$39.GNDVIA4, U$39.GNDVIA6, U$39.P$1, U$39.P$5, U$39.P$6, U$39.P$10, U$40.GNDVIA1, U$40.GNDVIA3, U$40.GNDVIA4, U$40.GNDVIA6, U$40.P$1, U$40.P$5, U$40.P$6, U$40.P$10, U$41.GNDVIA1, U$41.GNDVIA3, U$41.GNDVIA4, U$41.GNDVIA6, U$41.P$1, U$41.P$5, U$41.P$6, U$41.P$10, U$42.4
GND7: C8.2, U$43.GNDVIA1, U$43.GNDVIA3, U$43.GNDVIA4, U$43.GNDVIA6, U$43.P$1, U$43.P$5, U$43.P$6, U$43.P$10, U$44.GNDVIA1, U$44.GNDVIA3, U$44.GNDVIA4, U$44.GNDVIA6, U$44.P$1, U$44.P$5, U$44.P$6, U$44.P$10, U$45.GNDVIA1, U$45.GNDVIA3, U$45.GNDVIA4, U$45.GNDVIA6, U$45.P$1, U$45.P$5, U$45.P$6, U$45.P$10, U$46.GNDVIA1, U$46.GNDVIA3, U$46.GNDVIA4, U$46.GNDVIA6, U$46.P$1, U$46.P$5, U$46.P$6, U$46.P$10, U$47.GNDVIA1, U$47.GNDVIA3, U$47.GNDVIA4, U$47.GNDVIA6, U$47.P$1, U$47.P$5, U$47.P$6, U$47.P$10, U$48.4
GND8: C9.2, U$49.GNDVIA1, U$49.GNDVIA3, U$49.GNDVIA4, U$49.GNDVIA6, U$49.P$1, U$49.P$5, U$49.P$6, U$49.P$10, U$50.GNDVIA1, U$50.GNDVIA3, U$50.GNDVIA4, U$50.GNDVIA6, U$50.P$1, U$50.P$5, U$50.P$6, U$50.P$10, U$51.GNDVIA1, U$51.GNDVIA3, U$51.GNDVIA4, U$51.GNDVIA6, U$51.P$1, U$51.P$5, U$51.P$6, U$51.P$10, U$52.GNDVIA1, U$52.GNDVIA3, U$52.GNDVIA4, U$52.GNDVIA6, U$52.P$1, U$52.P$5, U$52.P$6, U$52.P$10, U$53.GNDVIA1, U$53.GNDVIA3, U$53.GNDVIA4, U$53.GNDVIA6, U$53.P$1, U$53.P$5, U$53.P$6, U$53.P$10, U$54.4
GND9: C10.2, U$55.GNDVIA1, U$55.GNDVIA3, U$55.GNDVIA4, U$55.GNDVIA6, U$55.P$1, U$55.P$5, U$55.P$6, U$55.P$10, U$56.GNDVIA1, U$56.GNDVIA3, U$56.GNDVIA4, U$56.GNDVIA6, U$56.P$1, U$56.P$5, U$56.P$6, U$56.P$10, U$57.GNDVIA1, U$57.GNDVIA3, U$57.GNDVIA4, U$57.GNDVIA6, U$57.P$1, U$57.P$5, U$57.P$6, U$57.P$10, U$58.GNDVIA1, U$58.GNDVIA3, U$58.GNDVIA4, U$58.GNDVIA6, U$58.P$1, U$58.P$5, U$58.P$6, U$58.P$10, U$59.GNDVIA1, U$59.GNDVIA3, U$59.GNDVIA4, U$59.GNDVIA6, U$59.P$1, U$59.P$5, U$59.P$6, U$59.P$10, U$60.4
GND10: C11.2, U$61.GNDVIA1, U$61.GNDVIA3, U$61.GNDVIA4, U$61.GNDVIA6, U$61.P$1, U$61.P$5, U$61.P$6, U$61.P$10, U$62.GNDVIA1, U$62.GNDVIA3, U$62.GNDVIA4, U$62.GNDVIA6, U$62.P$1, U$62.P$5, U$62.P$6, U$62.P$10, U$63.GNDVIA1, U$63.GNDVIA3, U$63.GNDVIA4, U$63.GNDVIA6, U$63.P$1, U$63.P$5, U$63.P$6, U$63.P$10, U$64.GNDVIA1, U$64.GNDVIA3, U$64.GNDVIA4, U$64.GNDVIA6, U$64.P$1, U$64.P$5, U$64.P$6, U$64.P$10, U$65.GNDVIA1, U$65.GNDVIA3, U$65.GNDVIA4, U$65.GNDVIA6, U$65.P$1, U$65.P$5, U$65.P$6, U$65.P$10, U$66.4
GND11: C12.2, U$67.GNDVIA1, U$67.GNDVIA3, U$67.GNDVIA4, U$67.GNDVIA6, U$67.P$1, U$67.P$5, U$67.P$6, U$67.P$10, U$68.GNDVIA1, U$68.GNDVIA3, U$68.GNDVIA4, U$68.GNDVIA6, U$68.P$1, U$68.P$5, U$68.P$6, U$68.P$10, U$69.GNDVIA1, U$69.GNDVIA3, U$69.GNDVIA4, U$69.GNDVIA6, U$69.P$1, U$69.P$5, U$69.P$6, U$69.P$10, U$70.GNDVIA1, U$70.GNDVIA3, U$70.GNDVIA4, U$70.GNDVIA6, U$70.P$1, U$70.P$5, U$70.P$6, U$70.P$10, U$71.GNDVIA1, U$71.GNDVIA3, U$71.GNDVIA4, U$71.GNDVIA6, U$71.P$1, U$71.P$5, U$71.P$6, U$71.P$10, U$72.4
GND12: C13.2, U$73.GNDVIA1, U$73.GNDVIA3, U$73.GNDVIA4, U$73.GNDVIA6, U$73.P$1, U$73.P$5, U$73.P$6, U$73.P$10, U$74.GNDVIA1, U$74.GNDVIA3, U$74.GNDVIA4, U$74.GNDVIA6, U$74.P$1, U$74.P$5, U$74.P$6, U$74.P$10, U$75.GNDVIA1, U$75.GNDVIA3, U$75.GNDVIA4, U$75.GNDVIA6, U$75.P$1, U$75.P$5, U$75.P$6, U$75.P$10, U$76.GNDVIA1, U$76.GNDVIA3, U$76.GNDVIA4, U$76.GNDVIA6, U$76.P$1, U$76.P$5, U$76.P$6, U$76.P$10, U$77.GNDVIA1, U$77.GNDVIA3, U$77.GNDVIA4, U$77.GNDVIA6, U$77.P$1, U$77.P$5, U$77.P$6, U$77.P$10, U$78.4
GND13: C14.2, U$79.GNDVIA1, U$79.GNDVIA3, U$79.GNDVIA4, U$79.GNDVIA6, U$79.P$1, U$79.P$5, U$79.P$6, U$79.P$10, U$80.GNDVIA1, U$80.GNDVIA3, U$80.GNDVIA4, U$80.GNDVIA6, U$80.P$1, U$80.P$5, U$80.P$6, U$80.P$10, U$81.GNDVIA1, U$81.GNDVIA3, U$81.GNDVIA4, U$81.GNDVIA6, U$81.P$1, U$81.P$5, U$81.P$6, U$81.P$10, U$82.GNDVIA1, U$82.GNDVIA3, U$82.GNDVIA4, U$82.GNDVIA6, U$82.P$1, U$82.P$5, U$82.P$6, U$82.P$10, U$83.GNDVIA1, U$83.GNDVIA3, U$83.GNDVIA4, U$83.GNDVIA6, U$83.P$1, U$83.P$5, U$83.P$6, U$83.P$10, U$84.4
GND14: C15.2, U$85.GNDVIA1, U$85.GNDVIA3, U$85.GNDVIA4, U$85.GNDVIA6, U$85.P$1, U$85.P$5, U$85.P$6, U$85.P$10, U$86.GNDVIA1, U$86.GNDVIA3, U$86.GNDVIA4, U$86.GNDVIA6, U$86.P$1, U$86.P$5, U$86.P$6, U$86.P$10, U$87.GNDVIA1, U$87.GNDVIA3, U$87.GNDVIA4, U$87.GNDVIA6, U$87.P$1, U$87.P$5, U$87.P$6, U$87.P$10, U$88.GNDVIA1, U$88.GNDVIA3, U$88.GNDVIA4, U$88.GNDVIA6, U$88.P$1, U$88.P$5, U$88.P$6, U$88.P$10, U$89.GNDVIA1, U$89.GNDVIA3, U$89.GNDVIA4, U$89.GNDVIA6, U$89.P$1, U$89.P$5, U$89.P$6, U$89.P$10, U$90.4
unnamed: C2.1, R3.2, U$12.3
unnamed: R4.1, U$12.1
unnamed: C3.1, R5.2, U$18.3
unnamed: R6.1, U$18.1
unnamed: C4.1, R7.2, U$24.3
unnamed: R8.1, U$24.1
unnamed: C5.1, R9.2, U$30.3
unnamed: R10.1, U$30.1
unnamed: C6.1, R11.2, U$36.3
unnamed: R12.1, U$36.1
unnamed: C7.1, R13.2, U$42.3
unnamed: R14.1, U$42.1
unnamed: C8.1, R15.2, U$48.3
unnamed: R16.1, U$48.1
unnamed: C9.1, R17.2, U$54.3
unnamed: R18.1, U$54.1
unnamed: C10.1, R19.2, U$60.3
unnamed: R20.1, U$60.1
unnamed: C11.1, R21.2, U$66.3
unnamed: R22.1, U$66.1
unnamed: C12.1, R23.2, U$72.3
unnamed: R24.1, U$72.1
unnamed: C13.1, R25.2, U$78.3
unnamed: R26.1, U$78.1
unnamed: C14.1, R27.2, U$84.3
unnamed: R28.1, U$84.1
unnamed: C15.1, R29.2, U$90.3
unnamed: R30.1, U$90.1
S$6: E$201.P$4, U$93.P$1, U$93.P$5
S$7: E$201.P$2, U$93.P$3
S$8: E$201.P$3, PROG2.MP
S$9: E$204.P$4, U$94.P$1, U$94.P$5
S$11: E$204.P$2, U$94.P$3
S$12: E$204.P$3, PROG3.MP
VCC2: E$201.P$1, U$93.P$7, U$93.P$9
VCC3: E$204.P$1, U$94.P$7, U$94.P$9

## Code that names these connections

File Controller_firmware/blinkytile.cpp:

#include "WProgram.h"
#include "pins_arduino.h"
#include "blinkytile.h"

void initBoard() {
    pinMode(BUTTON_A_PIN, INPUT);
    pinMode(BUTTON_B_PIN, INPUT);
    pinMode(STATUS_LED_PIN, OUTPUT);
    pinMode(POWER_ENABLE_PIN, OUTPUT);

    pinMode(FLASH_CS_PIN, OUTPUT);
    pinMode(ADDRESS_P_PIN, OUTPUT);
    pinMode(DATA_OUT_PIN, OUTPUT);

    setStatusLed(255);
    disableOutputPower();
}

void setStatusLed(uint8_t value) {
    analogWrite(STATUS_LED_PIN, (255-value));
}

void enableOutputPower() {
    digitalWrite(POWER_ENABLE_PIN, LOW);
}

void disableOutputPower() {
    digitalWrite(POWER_ENABLE_PIN, HIGH);
}

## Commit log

2014-06-20 Proof of concept version; seems to work!
2014-06-20 Move all components to top side
2014-06-20 Add stop mask to test points.
2014-06-22 Add silk, place order for RevB version
2014-07-07 Update for RevC
2014-08-19 Switch to WS2822S module, bump to RevD.
2014-08-20 Add panel design prototype
2014-08-20 Rename to BlinkyTile
2014-09-01 Rev E of pcb, control pcb
2014-09-01 Put address line on edge, tighten R and C positions
2014-09-02 Add RevF panel design, as submitted
2014-09-02 Bump to RevF: shaped solder masks for different signals
2014-09-04 Add Test Jig PCB from Sam, first pass at firmware
2014-09-05 Update channel count to match board
2014-09-09 Add tile test/address programming jig
2014-10-06 Add plastic pyramid design
2014-10-11 Add Controller from Sam
2014-10-11 Rev 5 panel design by Sam
2014-10-11 Rev 6 panel design (as submitted for prototype PCB)
2014-10-11 PCB design: add dimensions
2014-10-11 Update test program
2014-10-14 RevB of tester board: add 5v buffers
2014-10-14 added injection moldable version of pyramid topper
2014-10-15 Update controller board design for RevA
2014-10-20 Switch to smaller processor, change FLASH_CS to hardware CS pin
2014-10-21 Rev J panel: Add larger spaces in centers between tiles, tighten up edges.
2014-10-22 Update to RevB controller from Sam
2014-10-23 Add extra vias for input power to the 5v mosfet
2014-10-23 Remove outdated tile controller
2014-10-23 Bring over firmware from leoblinky
2014-10-23 Update to use bitbanging DMX routine.
2014-10-23 Add higher-speed DMX test. Doesn't conform to a standard.
2014-10-24 Add bootloader, serial receive routine
2014-10-24 Modify bootloader to support RevA LED and DFU-on-button-press
2014-10-24 Rename firmware directory.
2014-10-25 Bootloader: Go into DFU mode if both buttons are held down during poweron
2014-10-25 Add button inputs, another pattern
2014-10-25 Play-from flash
2014-10-25 Use SPI hardware chip select (requires board mod: analog in to flash CS)
2014-10-25 Comment out CS pin, for deletion later.
2014-10-26 Bugfix: use correct frame length when reading animations
2014-10-26 PCB updates: Drop pullup resistors, change connector
2014-10-27 Updated controller and panel designs
2014-10-27 Updated controller board, by Sam
2014-10-28 Update controller: move R5 to 3.3v, reduce panel size, move more routing to top layer
2014-10-28 Add stopmask under processor ground, fix silkscreen
2014-10-29 added blinkytile-pcb
2014-10-30 made snap legs longer and thinner, added nubs for secure fit
2014-10-30 Added topper assembly
2014-10-30 shortened the width of snaps to ensure they have enough room to flex on insertion
2014-10-30 added 2nd set to assembly for verifying different angles of assembly
2014-11-02 Controller: Change .1" header footprint to Sparkfun version, make text larger
2014-11-03 Prepare for a 64k system; fix timing bug in display code
2014-11-03 Update panel
2014-11-03 Update panel
    - fixed connector board error
    - added fiducial marker at corner
    - removed mounting holes at side
    - removed 2 connector boards on panel
    - added remark for blinkyTile signal
2014-11-03 Fix error on text
2014-11-03 Attempt to port to mk20dn64 (no flexram, 64k flash)
2014-11-03 Update bootloader to support longword-based uploads (ugh!)
2014-11-03 Update pin definitions for RevB
2014-11-04 Controller: move end of 3.3v trace to improve grounding, replace switch, resize 5v line
2014-11-04 Change 4p output connector, push switches in a bit
2014-11-04 Update flash type, add .254mm isolation on top&bottom copper, general cleanup
2014-11-04 beef up power line widths
2014-11-05 Add ferrite beads, move the fuse to the ouput.
2014-11-06 Tidy schematic and add values to ferrites, crystal
2014-11-06 Enlarge via sizes to .3mm
2014-11-07 Controller: Switch back to 208 package for flash chip
2014-11-07 Rename pcb directories
2014-11-11 Add protection diode, JST battery connector, tweak positions for manufacturability, redo silk
2014-11-11 Rev M panel from Sam
2014-11-13 New panel artwork
2014-11-15 Update firmware to support spansion flash
2014-11-15 Remove flexram section from link table, add 8M variant of winbond flash
2014-11-15 Remove RevA definitions
2014-11-18 Move tile test jig location
2014-11-18 Add testjig from Fadecandy project (thanks Beth!)
2014-11-18 Clean up schematic layout
2014-11-20 Add sector descriptor format
2014-11-21 Getting the tile test rig working: small circuit design issues.
2014-11-23 Update firmware to latest teensyduino includes, switch to serial for comms
2014-11-23 Disable C++ interface in usb_serial, we can has usb serial now!
2014-11-23 Controller boar design, as released.
2014-11-23 Controller pcb, as fixed
2014-11-23 Add alternate markings for the silkscreen
2014-11-23 Update testjig readme
2014-11-23 Add test jig design for controller
2014-11-25 Update USB descriptors to have endpoints for serial, bulk transfer (fadecandy), and DFU.
2014-11-25 DFU mode works with CDC ACM
2014-11-25 Add notes for reworking controller testjig pcb
2014-11-25 Add debug lights to the controller testjig fw, update defines
2014-11-25 Update production test to minimal working function
2014-11-26 Add flash test to production firmware
2014-11-26 Also erase the external flash, as a matter of course.
2014-11-26 Program blinkyTile address on panel by simple button press
2014-11-26 Production test: use longword instead of flexram for writing
2014-11-27 Add button test, board pin short tests, output tests
2014-11-27 Production version!
2014-11-29 Small bugfix to test rig firmware
2014-11-29 controller test: blink during external flash test
2014-11-29 Firmware bugfix: ping watchdog while writing to flash, to prevent tripping it when waiting for large flash to erase
2014-11-29 Update flash library name to reflect support for multiple flash types
2014-12-01 Fix string names of usb interfaces, remove teensyduino reset sequence, DFU reset broken?
2014-12-01 Change product code to 0x6666
2014-12-04 BlinkyTile TestRig for production
    - Bugs fixed
    - automatic program address (1-14) then verify address and test color
    - added erase command
    - added test color command
2014-12-04 Updated Test LED status
2014-12-05 Clean up flash class a little more
2014-12-05 Get sectordescriptor compiling
2014-12-05 Add some simple serial commands to test the sector manager- seems to work.
2014-12-07 Create/delete files on the flash memory
2014-12-08 Increase tile routing size as per manufacturers specification
2014-12-08 Add write function to sector descriptor
2014-12-08 Bugfix: toggle flash write protect between writes/deletes
2014-12-08 Hook nofatstorage up to animations, default animation mostly works
2014-12-08 Add serial number hasher from Fadecandy
2014-12-10 Start to patch in fadecandy love
2014-12-10 Get things compiled again, serial working but fc not working.
2014-12-10 Bump up the bootloader speed by polling internally
2014-12-10 V1 bootloader
2014-12-10 Shell of an FC interface present, but works with serial. defer for now.
2014-12-10 Add address programmer function
2014-12-11 Move single character hack debug mode out of main
2014-12-11 Attempted (and failed) speedups to the production test
2014-12-11 Clean up gitignore to hide some common temp files
2014-12-11 Fix some whitespace
2014-12-11 Rewrite serial input routine
2014-12-11 Fix up the DMX timing a bit, address programming.
2014-12-11 Update bootloader with Openmoko-gifted PID
2014-12-11 Start building out the command protocol
2014-12-11 Now we're writing and reading!
2014-12-11 And we can't write a big file yet!
2014-12-12 Snapshot of broken upload code
2014-12-12 Narrowed it down to file page write
2014-12-12 fileWritePage seems to work again.
2014-12-12 Non-sector spanning flash read works, new test for sector spanning
2014-12-12 File read test of random size reads passes
2014-12-12 Trying to write an animation
2014-12-12 Animation looks ok via visual inspection, but isn't coming through
2014-12-12 Store and playback animtation 0 works!
2014-12-12 Multiple animations partially works
2014-12-12 Add file type command and file delete command
2014-12-12 Animation program
2014-12-12 Update tile testrig to support 15+ address programming
2014-12-13 BlinkyTile production bootloader and firmware
2014-12-13 Update production firmware (add animation type field)
2014-12-13 Add new animations
2014-12-20 Check in latent python code `
2014-12-26 Add signed windows driver
2015-02-17 Update test rig to support >99 addresses, interactively changing range
2015-03-04 Buggy support for fadecandy (high framerates lock up USB)
2015-03-06 Working on hardware dmx
2015-03-07 Pulse trains work
2015-03-07 Mostly working dma version
2015-03-07 DMA working!
2015-03-13 Bump version to .2
2015-03-13 Add V.2 firmware: enables Fadecandy endpoint support, DMA-based DMX output
2015-03-14 Improving buffering for DMX
2015-03-14 Bugfix: restore brightness button with hardware DMX output
2015-03-15 Throw in an 8-bit brightness correction table
2015-03-23 Update firmware filename, default firmware for animation programmer
2015-03-23 Add first-pass support of ws2812 strips
2015-03-23 WS2812 bugfix, get rid of extraneous pulse at end of cycle
2015-03-23 Resize some variables, looks like we can do at least 120 pixels in a chain.
2015-03-24 Polyglot go! first workings of a runtime switchable DMA engine
2015-03-24 Pushbutton change of LED type!
2015-03-24 LPD8806 almost works
2015-03-26 Bugfix: invert clock in lpd8806, don't assert DMA channel start
2015-03-26 Add APA102 support
2015-03-26 Adjust timings for LPD8806, APA102
2015-03-28 Enable compile time double-buffer switch
2015-03-28 Swap DMA interrupts on APA102 and LPD0086 so we can bump SPI output to 3.5MHz
2015-03-28 Fix color ordering
2015-03-30 Re-sign driver
2015-03-30 Add commented-out double buffer option
2015-03-31 Restore partial serial functionality. Still can't handle transfers >64 bytes.
2015-04-02 Add slim controller design from Sam
2015-04-02 Rework board to be 29mm, use 0603 package for main cap, add bottom side pad for VUSB, improve +5V routing
2015-04-02 RevA tiny controller
2015-04-13 Add some messages to animationProgrammer
2015-05-31 Add python script to load an animation from an image file.
2015-05-31 Add image programmer script (was in polyglot)
2015-08-25 Update address programmer to work with addresses >14
2015-08-26 Add disorient pattern example
2015-11-17 Add hexagon design
2015-11-17 Add art to single-tile pentagon
2016-02-28 Control Board: make USB pads longer, update silkscreen (RevE)
2016-02-28 Art files for Controller PCB Rev E
2016-10-25 Add travis integration file
2016-10-25 Fix file case problem
2016-12-22 Move test files into new directories
2016-12-22 More rearranging
2016-12-22 Update file locations
2016-12-22 Remove outdated tool
2016-12-22 Update note about board
2016-12-22 Add note about how to enable floating-point printf
2016-12-22 Add debugging info for voltage tests, fix tolerances
2016-12-22 Remove old physical design files
2016-12-22 Rename more directories
2016-12-22 Add some files that were floating around
2016-12-22 Remove temp file
2016-12-22 Update animationProgrammer example
2016-12-24 Nonworking address programmer
2016-12-30 Update so that WS2821 address programming works
2016-12-30 Remove WS2822S/WS2821 address programming selection since both are compatible
2017-01-16 Enable multi-address programming
2017-01-16 Bump to 170 LED
2017-01-16 Adjust to program 3 addresses, set max LED to 170
2017-01-16 Add 1.0.1 binaries (for WS2821)
2025-08-05 Update address programmer for python3
2025-08-08 Address programmer: auto-increment after programming
